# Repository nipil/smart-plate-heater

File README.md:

# smart-plate-heater

A weight-based, smart plate heater for ease of use and safety

- The posh wooden plate that the user sees !

- The back "measuring foot"
  - holding all the wieght in a 3-points-of-contact setup
  - maximum 5kg vertically on the back, so an average of 10kg in center
  - the back feet do nothing except prevent tumbling

- due to the sensitivity of the voltages used for measuring using a strain gauge, the pre-processing must be done locally... plus the panel can be done locally too and everything fits in the 8 wires of the network cable

The target "perfboard pcb", with only 3 additional wires (solid core, 26 AWG, ptfe isolated wires)

Only 3 shrink fit insulation patches, where i forgot to make multi-level "manhattan-style" routing

Everything fits in a 80x80 mm derivation box, even if it is crowded. And i can still easily take the microcontroller out, for in-situ calibration with another "debugging" MCU, and re-program the "target" MCU before sticking it back in.

Finally i managed to make both output exit on the same side, and the input on the opposite side, which is pretty neat.

## Schematic and "perfboard" PCB

The way the main board works and AC safety is done in the derivation box

I always prepare my perfboard routing on a appropriately sized PCB

The way the appliance and user panel is wired

## Hardware

Target board on perfboard (uses 8mA@3V3 at idle and 80ma@3V3 when relay is on)

- PIC 10F200-family microcontroller (here a 202 in SOP-23 a DIP breakout board) from rs-online.com

- 500mA 5x20 fuse and fuse holder (oversized, the whole thing draws less than 0.35 W at full load)

- varistor 10D561K (transient voltage suppressor TVS) ot protect the circuit from grid surges

- HLK-PM03 3W 240VAC to 3.3VDC converter (isolated)

- HX711 breakout board (purple with holes for fixturing

- Beam-type load cell (maximum 5KG)

- 3.3V relay board (active low, floating high)

- network port breakout board, and a network cable to cut

- normally open temporary button, single pole single throw (SPST) rocker switch...
- screw terminals, 1/4W resistors, 5mm LED, headers,dc caps, 2N3904 NPN transitor...

For prototyping

- breadboard and dupont cables
- ESP32 DevKit 38 pins

- logic analyzer (salae clone)

Real wafeforms results in PulseView software from ESP prototype

- Macro waveforms to see sampling rate of HX711 breakout board (1 sample per 0.4 second = 2.5 Hz)

- Micro waveforms to check the clock and data timings (data transfer time is 115 micro-seconds)

## Pinouts

Using a PIC10F202 as microcontroller

Target perfboard using PIC10F202 SOT-23-to-DIP pinout

    PIN 1 = GP0 = OUT_HEAT  PIN 6 = GP3 = IN_BUTTON
    PIN 2 = VSS (-)         PIN 5 = VDD (+)
    PIN 3 = GP1 = OUT_CLK   PIN 4 = GP2 = IN_DATA

Arduino prototype on ESP32 DevKit pinout

    G14 = OUT_HEAT
    G25 = OUT_CLOCK
    G13 = IN_DATA
    G34 = IN_BUTTON

## kicad folder

Design for electronics and target solderboard in a box

## mplab.x folder

PIC IDE, and C code built with XC8 compiler to generate HEX file

- [Pre-compiled HEX file for a PIC10F202 microcontroller](mplab.X/pic10f202-production.hex)
- which you can program using my homemade [Arduino-UNO-based simple pic programmer](https://github.com/nipil/arduino-simple-pic-programmer)

### Debugging

Go to `Tools/Options/Embedded`

- debug reset `reset vector`
- debug startup `halt at reset vector`
- activate stimulus (*.scl) file
- use simulator to debug

### Chip fuses

Go to `Window/Target Memory View/Configuration bits`

- disable MCLRE to be able to use GP3

## arduino-esp-prototype-software folder

This is an archived folder for an arduino framework, ESP32-devboard-based prototype

Achieved goals :

- verify that everything works on 3.3V
- discover raw values for "empty" aparatus
- discover raw values for "edge" beam strain gage
- discover effect of the weight of the cable (!)
- discover the "one kilogram on center" desired threshold
- verify light / transistor / relay working when desired
- verify values upon cable disconnection
- verify disconnection disabling
- verify negative/zero HX711 values disabling
- verify reset conditions disabling
- verify heat triggering by button when above threshold
- verify heat disabling when going under threshold

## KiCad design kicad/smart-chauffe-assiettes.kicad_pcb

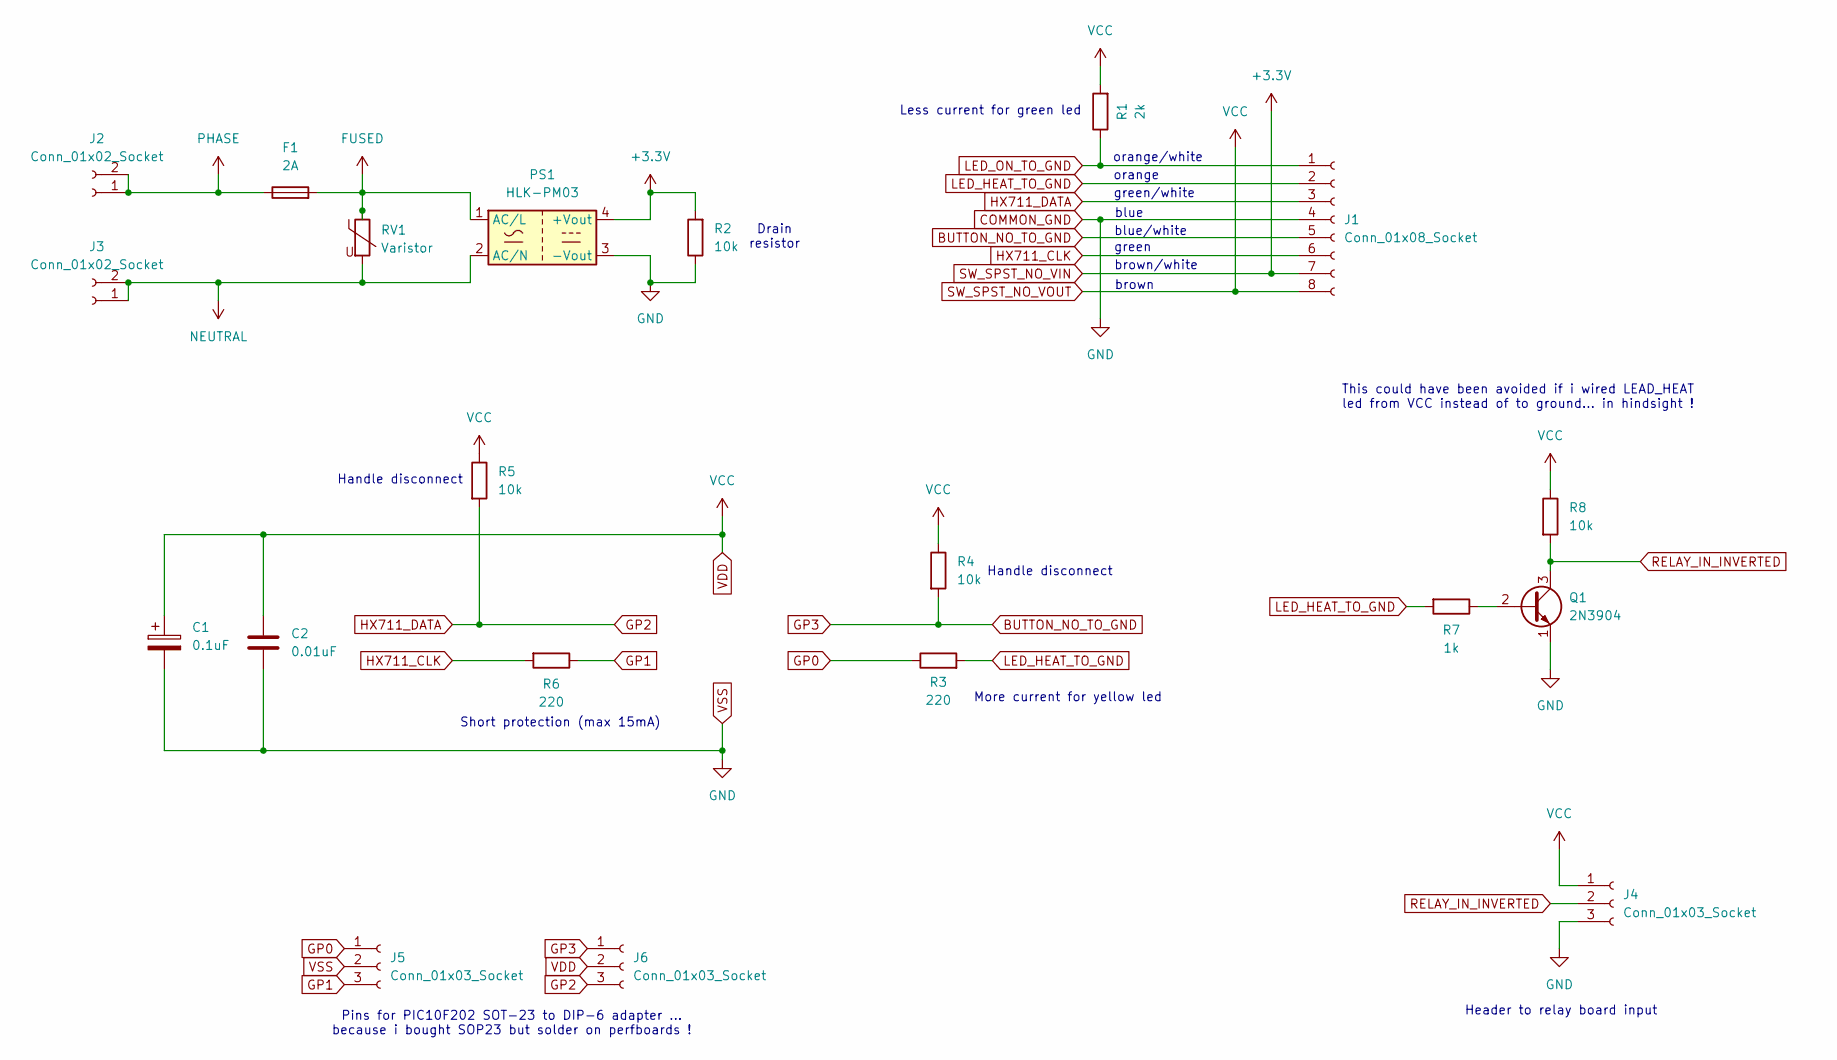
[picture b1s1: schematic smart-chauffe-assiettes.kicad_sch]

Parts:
C1: 0.1uF; CP_Radial_D4.0mm_P1.50mm
C2: 0.01uF; C_Disc_D3.0mm_W2.0mm_P2.50mm
F1: 2A; Fuseholder_Clip-5x20mm_Keystone_3518P_Inline_P23.11x6.76mm_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
J1: Conn_01x08_Socket; PinHeader_1x08_P2.54mm_Vertical
J2, J3: Conn_01x02_Socket; TerminalBlock_Phoenix_MKDS-1,5-2-5.08_1x02_P5.08mm_Horizont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
J4: Conn_01x03_Socket; TerminalBlock_Phoenix_MKDS-1,5-3-5.08_1x03_P5.08mm_Horizont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
J5, J6: Conn_01x03_Socket; PinSocket_1x03_P2.54mm_Vertical
PS1: HLK-PM03; Converter_ACDC_Hi-Link_HLK-PMxx
Q1: 2N3904; TO-92_Inline_Wide
R1: 2k; R_Axial_DIN0207_L6.3mm_D2.5mm_P2.54mm_Vertical
R2: 10k; R_Axial_DIN0207_L6.3mm_D2.5mm_P7.62mm_Horizontal
R3, R6: 220; R_Axial_DIN0207_L6.3mm_D2.5mm_P2.54mm_Vertical
R4, R5, R8: 10k; R_Axial_DIN0207_L6.3mm_D2.5mm_P2.54mm_Vertical
R7: 1k; R_Axial_DIN0207_L6.3mm_D2.5mm_P2.54mm_Vertical
RV1: Varistor; RV_Disc_D12mm_W7.5mm_P7.5mm

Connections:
BUTTON_NO_TO_GND: J1.5, J6.1, R4.2
COMMON_GND: C1.2, C2.2, J1.4, J4.3, J5.2, PS1.3 (-Vout), Q1.1 (E), R2.1
FUSED: F1.2, PS1.1 (AC/L), RV1.1
GP0: J5.1, R3.1
GP1: J5.3, R6.1
GP2: J1.3, J6.3, R5.2
HX711_CLK: J1.6, R6.2
LED_HEAT_TO_GND: J1.2, R3.2, R7.2
LED_ON_TO_GND: J1.1, R1.1
NEUTRAL: J3.1, J3.2, PS1.2 (AC/N), RV1.2
unnamed: Q1.2 (B), R7.1
PHASE: F1.1, J2.1, J2.2
RELAY_IN_INVERTED: J4.2, Q1.3 (C), R8.2
SW_SPST_NO_VIN: J1.7, PS1.4 (+Vout), R2.2
SW_SPST_NO_VOUT: C1.1, C2.1, J1.8, J4.1, J6.2, R1.2, R4.1, R5.1, R8.1

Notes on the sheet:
brown
Less current for green led
Short protection (max 15mA)
blue
Drain resistor
More current for yellow led
Handle disconnect
Pins for PIC10F202 SOT-23 to DIP-6 adapter ... because i bought SOP23 but solder on perfboards !
orange
orange/white
green
brown/white
Header to relay board input
green/white
This could have been avoided if i wired LEAD_HEAT led from VCC instead of to ground... in hindsight !
blue/white

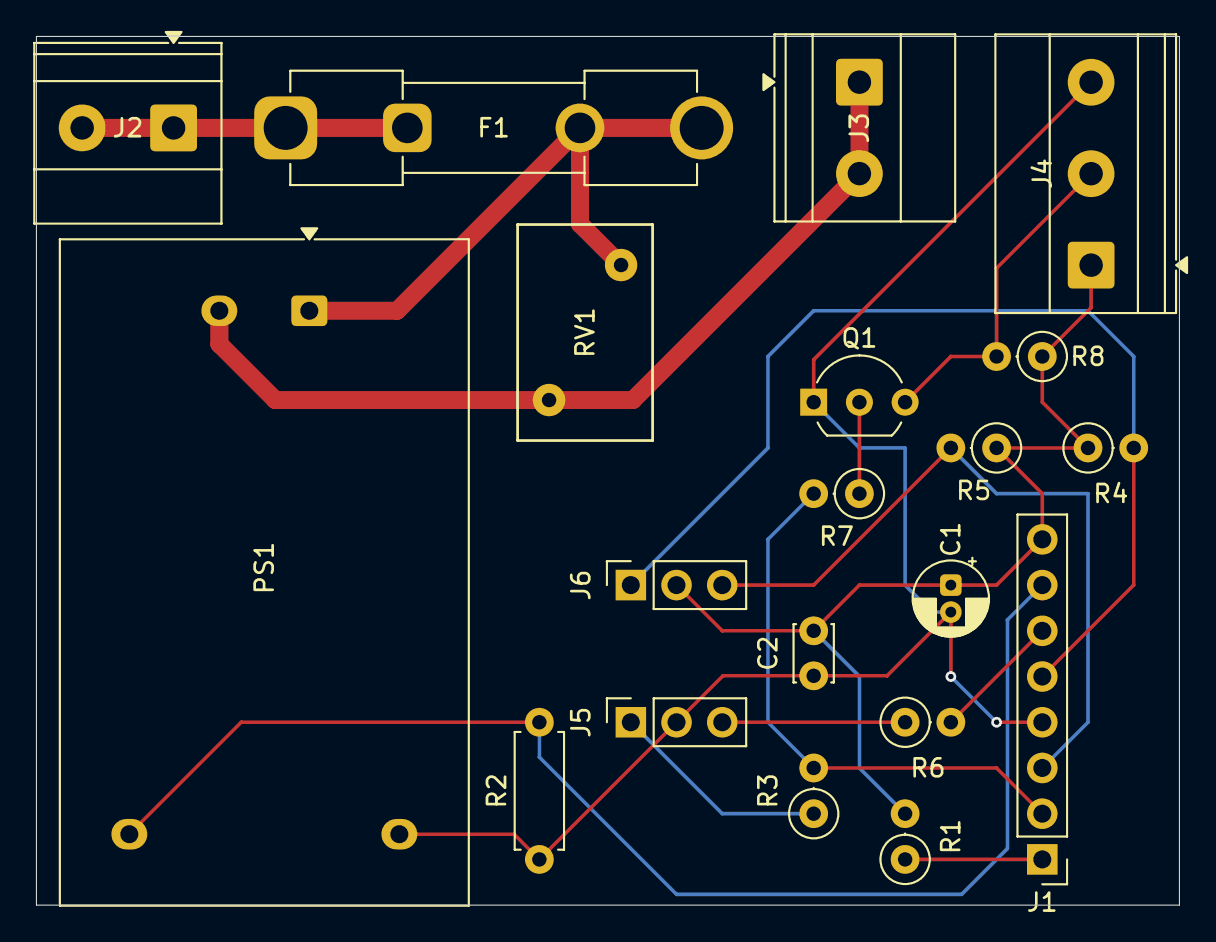
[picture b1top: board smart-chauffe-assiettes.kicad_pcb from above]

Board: 2 copper layers, 63.5 x 48.3 mm, 20 parts (0 on the bottom side), 15 nets.

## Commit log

2026-01-17 Project setup
2026-01-18 First try to read from inputs and write to outputs
2026-01-19 Play with stimulus and XC8 cycle-delay code-generating functions
2026-01-19 Play with inline vs function wait code
2026-01-21 First stab at codig the conversion workflow
2026-01-21 Compare with reference weight, and (de)activate opto
2026-01-24 Added final hardware calibration : raw 24 bit values
2026-01-25 Add working ESP32 3.3v prototype validated on breadboard
2026-01-25 Add first stab at schematic
2026-01-26 Fix path to readme file
2026-01-26 Finalize schematic : inverted relay and sop23-to-dip6 adapter
2026-01-26 Fix footprint for header to relay input
2026-01-26 First attempt at laying out the components
2026-01-26 Add text for design info and rename power networks
2026-01-26 Add custom rule for power networks
2026-01-26 First stab at routing
2026-01-28 Update PIC code to match the theoretical desired output
2026-01-28 Switch from shifting bits into an int32, to shifting into 3 uint8
2026-01-30 Adjusted "safety" threshold and "lifted" delta
2026-01-30 Rename INO file to match arduino convention
2026-01-30 Filter numerical data using kappa-sigma-median clipping
2026-01-30 Add vscode workspace
2026-01-30 Ignore generated files
2026-01-30 Ignore traces during simulation
2026-01-31 PIC/FIX: allow restarting after lowered weight (recorded)
2026-01-31 Added pinout for both boards
2026-01-31 Fix missing power trace and swap psu leads
2026-02-01 Enhance documentation with photos
2026-02-01 Add schematic documentation for appliance wiring (hx711/cell sym lib)
2026-02-01 Fix broken image links
2026-02-01 First release of the HEX file for PIC10F202
2026-02-08 Add finished photos of derivation box and connections
